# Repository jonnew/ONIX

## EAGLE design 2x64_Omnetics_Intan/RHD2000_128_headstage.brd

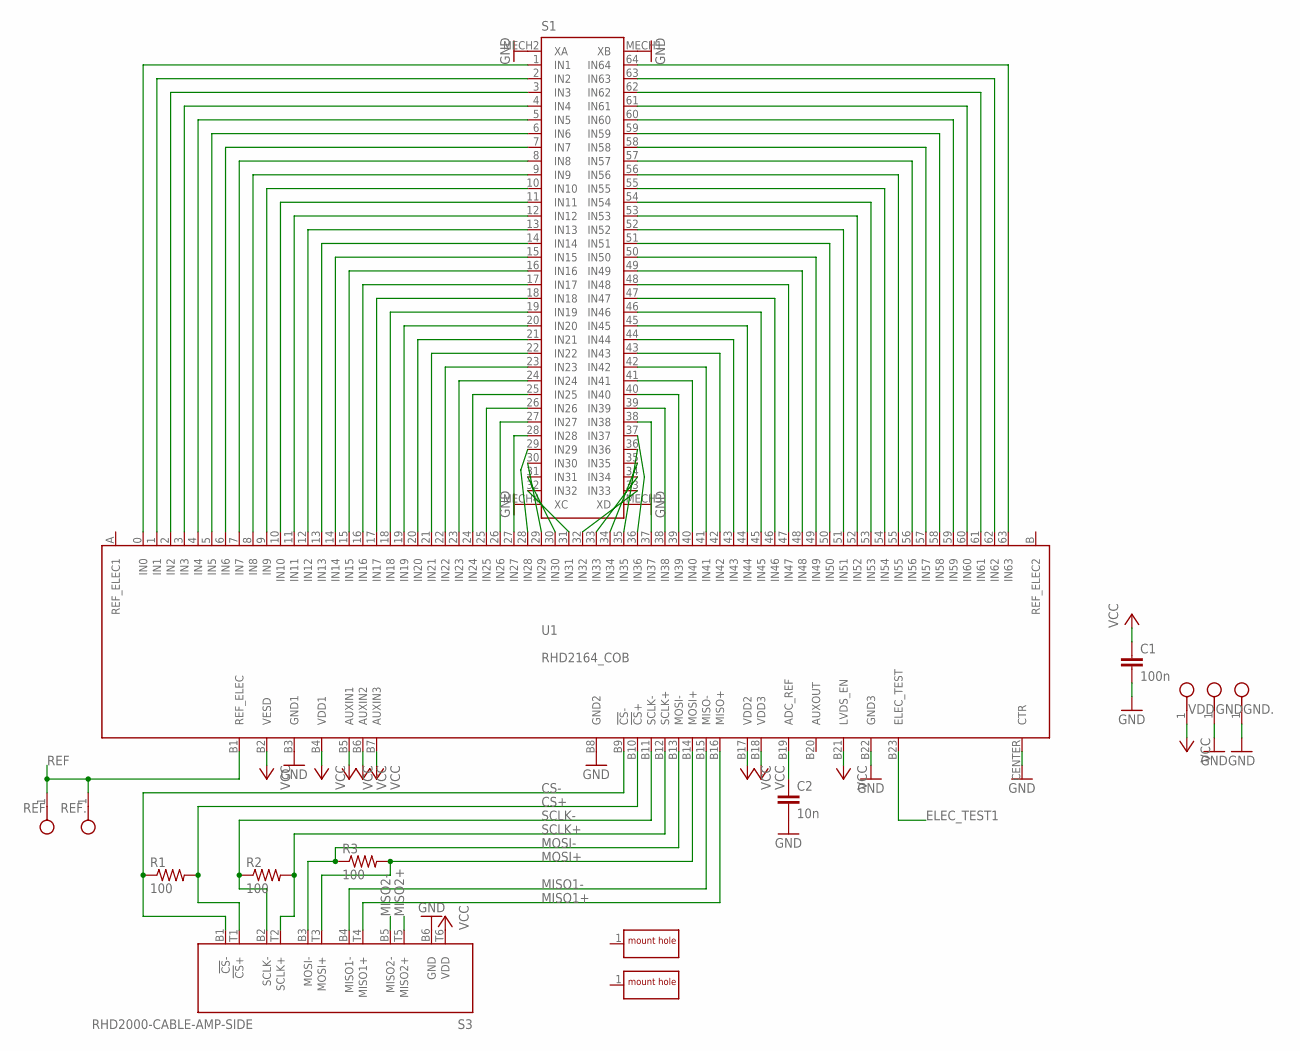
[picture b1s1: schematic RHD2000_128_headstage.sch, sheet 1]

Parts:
C1: 100n; 0402
C2: 10n; 0201
GND, GND.: TESTPOINT_SMALL
H1, H2: MOUNTING_HOLE_60MIL
R1, R2, R3: 100; 0201
REF, REF.: TESTPOINT_SMALL
S1: MOLEX_SLIMSTACK_64
S3: RHD2000-CABLE-AMP-SIDE; OMNETICS_PZN-12-AA
U1: RHD2164_COB
VDD: TESTPOINT_SMALL

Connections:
CS+: R1.2, S3.T1 (!CS!+), U1.B10 (!CS!+); also elsewhere on the board
CS-: R1.1, S3.B1 (!CS!-), U1.B9 (!CS!-); also elsewhere on the board
ELEC_TEST1: U1.B23 (ELEC_TEST); also elsewhere on the board
GND: C1.2, C2.2, GND.1, GND..1, S1.MECH1 (XB), S1.MECH2 (XA), S1.MECH3 (XD), S1.MECH4 (XC), S3.B6 (GND), U1.B3 (GND1), U1.B8 (GND2), U1.B22 (GND3), U1.CENTER (CTR); also elsewhere on the board
MISO1+: S3.T4 (MISO1+), U1.B16 (MISO+)
MISO1-: S3.B4 (MISO1-), U1.B15 (MISO-)
MISO2+: S3.T5 (MISO2+); also elsewhere on the board
MISO2-: S3.B5 (MISO2-); also elsewhere on the board
MOSI+: R3.2, S3.T3 (MOSI+), U1.B14 (MOSI+); also elsewhere on the board
MOSI-: R3.1, S3.B3 (MOSI-), U1.B13 (MOSI-); also elsewhere on the board
unnamed: S1.1 (IN1), U1.0 (IN0)
unnamed: S1.2 (IN2), U1.1 (IN1)
unnamed: S1.3 (IN3), U1.2 (IN2)
unnamed: S1.4 (IN4), U1.3 (IN3)
unnamed: S1.5 (IN5), U1.4 (IN4)
unnamed: S1.6 (IN6), U1.5 (IN5)
unnamed: S1.7 (IN7), U1.6 (IN6)
unnamed: S1.8 (IN8), U1.7 (IN7)
unnamed: S1.9 (IN9), U1.8 (IN8)
unnamed: S1.10 (IN10), U1.9 (IN9)
unnamed: S1.11 (IN11), U1.10 (IN10)
unnamed: S1.12 (IN12), U1.11 (IN11)
unnamed: S1.13 (IN13), U1.12 (IN12)
unnamed: S1.14 (IN14), U1.13 (IN13)
unnamed: S1.15 (IN15), U1.14 (IN14)
unnamed: S1.16 (IN16), U1.15 (IN15)
unnamed: S1.17 (IN17), U1.16 (IN16)
unnamed: S1.18 (IN18), U1.17 (IN17)
unnamed: S1.19 (IN19), U1.18 (IN18)
unnamed: S1.20 (IN20), U1.19 (IN19)
unnamed: S1.21 (IN21), U1.20 (IN20)
unnamed: S1.22 (IN22), U1.21 (IN21)
unnamed: S1.23 (IN23), U1.22 (IN22)
unnamed: S1.24 (IN24), U1.23 (IN23)
unnamed: S1.25 (IN25), U1.24 (IN24)
unnamed: S1.26 (IN26), U1.25 (IN25)
unnamed: S1.27 (IN27), U1.26 (IN26)
unnamed: S1.28 (IN28), U1.27 (IN27)
unnamed: S1.38 (IN38), U1.37 (IN37)
unnamed: S1.39 (IN39), U1.38 (IN38)
unnamed: S1.64 (IN64), U1.63 (IN63)
unnamed: S1.63 (IN63), U1.62 (IN62)
unnamed: S1.62 (IN62), U1.61 (IN61)
unnamed: C2.1, U1.B19 (ADC_REF)
unnamed: S1.61 (IN61), U1.60 (IN60)
unnamed: S1.60 (IN60), U1.59 (IN59)
unnamed: S1.59 (IN59), U1.58 (IN58)
unnamed: S1.58 (IN58), U1.57 (IN57)
unnamed: S1.57 (IN57), U1.56 (IN56)
unnamed: S1.56 (IN56), U1.55 (IN55)
unnamed: S1.55 (IN55), U1.54 (IN54)
unnamed: S1.54 (IN54), U1.53 (IN53)
unnamed: S1.53 (IN53), U1.52 (IN52)
unnamed: S1.52 (IN52), U1.51 (IN51)
unnamed: S1.51 (IN51), U1.50 (IN50)
unnamed: S1.50 (IN50), U1.49 (IN49)
unnamed: S1.49 (IN49), U1.48 (IN48)
unnamed: S1.48 (IN48), U1.47 (IN47)
unnamed: S1.47 (IN47), U1.46 (IN46)
unnamed: S1.46 (IN46), U1.45 (IN45)
unnamed: S1.45 (IN45), U1.44 (IN44)
unnamed: S1.44 (IN44), U1.43 (IN43)
unnamed: S1.43 (IN43), U1.42 (IN42)
unnamed: S1.42 (IN42), U1.41 (IN41)
unnamed: S1.41 (IN41), U1.40 (IN40)
unnamed: S1.40 (IN40), U1.39 (IN39)
unnamed: S1.32 (IN32), U1.31 (IN31)
unnamed: S1.31 (IN31), U1.30 (IN30)
unnamed: S1.30 (IN30), U1.29 (IN29)
unnamed: S1.29 (IN29), U1.28 (IN28)
unnamed: S1.33 (IN33), U1.32 (IN32)
unnamed: S1.34 (IN34), U1.33 (IN33)
unnamed: S1.35 (IN35), U1.34 (IN34)
unnamed: S1.36 (IN36), U1.35 (IN35)
unnamed: S1.37 (IN37), U1.36 (IN36)
REF: REF.1, REF..1, U1.B1 (REF_ELEC); also elsewhere on the board
SCLK+: R2.2, S3.T2 (SCLK+), U1.B12 (SCLK+); also elsewhere on the board
SCLK-: R2.1, S3.B2 (SCLK-), U1.B11 (SCLK-); also elsewhere on the board
VCC: C1.1, S3.T6 (VDD), U1.B2 (VESD), U1.B4 (VDD1), U1.B5 (AUXIN1), U1.B6 (AUXIN2), U1.B7 (AUXIN3), U1.B17 (VDD2), U1.B18 (VDD3), U1.B21 (LVDS_EN), VDD.1; also elsewhere on the board

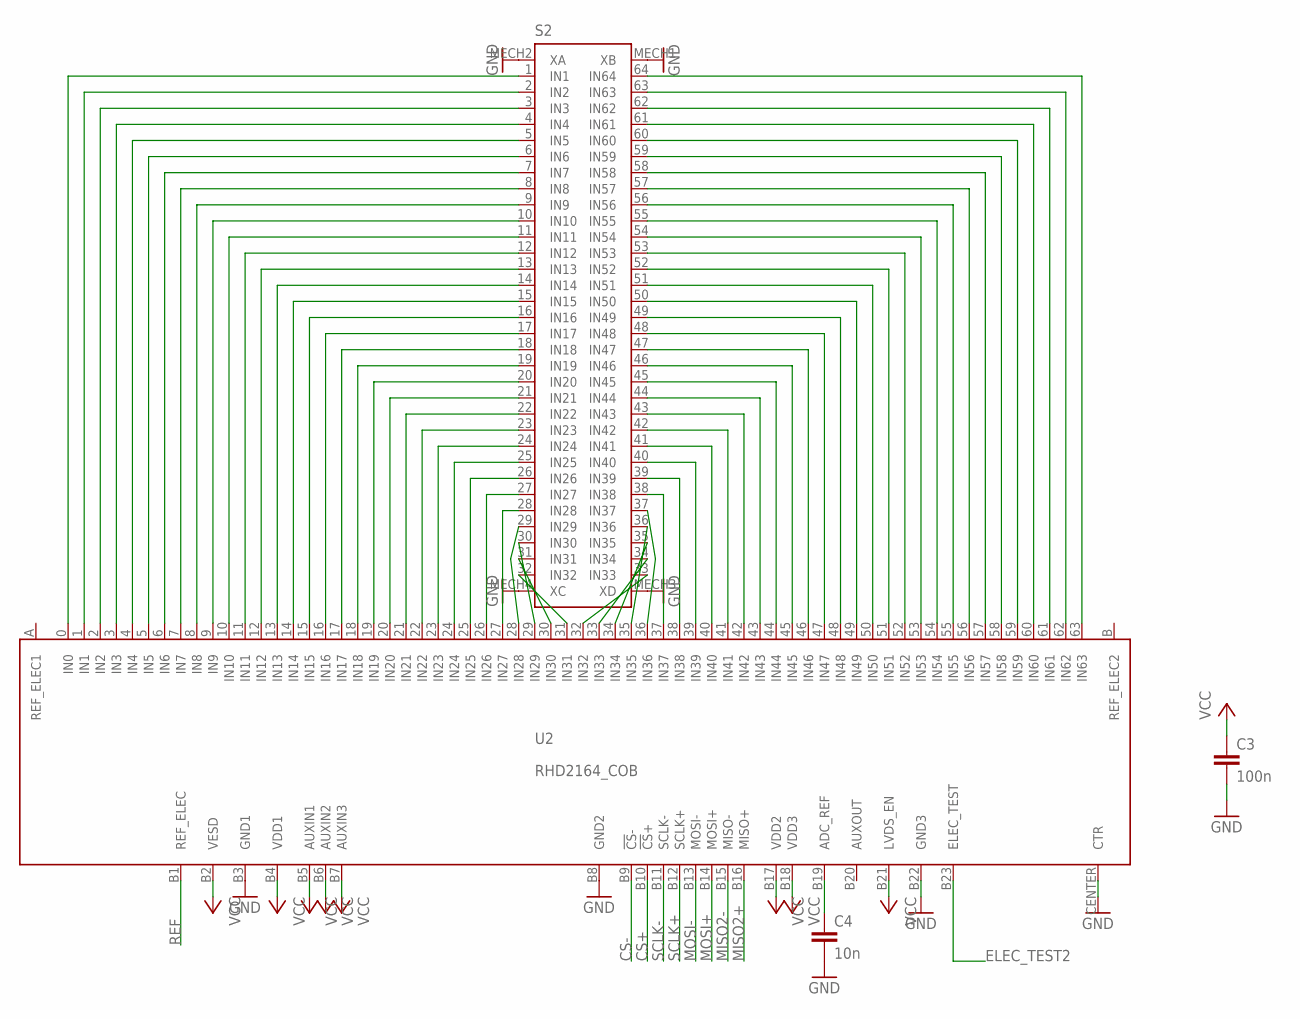
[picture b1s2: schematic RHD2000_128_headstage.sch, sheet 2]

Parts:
C3: 100n; 0402
C4: 10n; 0201
S2: MOLEX_SLIMSTACK_64
U2: RHD2164_COB

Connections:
CS+: U2.B10 (!CS!+); also elsewhere on the board
CS-: U2.B9 (!CS!-); also elsewhere on the board
ELEC_TEST2: U2.B23 (ELEC_TEST); also elsewhere on the board
GND: C3.2, C4.2, S2.MECH1 (XB), S2.MECH2 (XA), S2.MECH3 (XD), S2.MECH4 (XC), U2.B3 (GND1), U2.B8 (GND2), U2.B22 (GND3), U2.CENTER (CTR); also elsewhere on the board
MISO2+: U2.B16 (MISO+); also elsewhere on the board
MISO2-: U2.B15 (MISO-); also elsewhere on the board
MOSI+: U2.B14 (MOSI+); also elsewhere on the board
MOSI-: U2.B13 (MOSI-); also elsewhere on the board
unnamed: C4.1, U2.B19 (ADC_REF)
unnamed: S2.1 (IN1), U2.0 (IN0)
unnamed: S2.2 (IN2), U2.1 (IN1)
unnamed: S2.3 (IN3), U2.2 (IN2)
unnamed: S2.4 (IN4), U2.3 (IN3)
unnamed: S2.5 (IN5), U2.4 (IN4)
unnamed: S2.6 (IN6), U2.5 (IN5)
unnamed: S2.7 (IN7), U2.6 (IN6)
unnamed: S2.8 (IN8), U2.7 (IN7)
unnamed: S2.9 (IN9), U2.8 (IN8)
unnamed: S2.10 (IN10), U2.9 (IN9)
unnamed: S2.11 (IN11), U2.10 (IN10)
unnamed: S2.12 (IN12), U2.11 (IN11)
unnamed: S2.13 (IN13), U2.12 (IN12)
unnamed: S2.14 (IN14), U2.13 (IN13)
unnamed: S2.15 (IN15), U2.14 (IN14)
unnamed: S2.16 (IN16), U2.15 (IN15)
unnamed: S2.17 (IN17), U2.16 (IN16)
unnamed: S2.18 (IN18), U2.17 (IN17)
unnamed: S2.19 (IN19), U2.18 (IN18)
unnamed: S2.20 (IN20), U2.19 (IN19)
unnamed: S2.21 (IN21), U2.20 (IN20)
unnamed: S2.22 (IN22), U2.21 (IN21)
unnamed: S2.23 (IN23), U2.22 (IN22)
unnamed: S2.24 (IN24), U2.23 (IN23)
unnamed: S2.25 (IN25), U2.24 (IN24)
unnamed: S2.26 (IN26), U2.25 (IN25)
unnamed: S2.27 (IN27), U2.26 (IN26)
unnamed: S2.28 (IN28), U2.27 (IN27)
unnamed: S2.38 (IN38), U2.37 (IN37)
unnamed: S2.39 (IN39), U2.38 (IN38)
unnamed: S2.64 (IN64), U2.63 (IN63)
unnamed: S2.63 (IN63), U2.62 (IN62)
unnamed: S2.62 (IN62), U2.61 (IN61)
unnamed: S2.61 (IN61), U2.60 (IN60)
unnamed: S2.60 (IN60), U2.59 (IN59)
unnamed: S2.59 (IN59), U2.58 (IN58)
unnamed: S2.58 (IN58), U2.57 (IN57)
unnamed: S2.57 (IN57), U2.56 (IN56)
unnamed: S2.56 (IN56), U2.55 (IN55)
unnamed: S2.55 (IN55), U2.54 (IN54)
unnamed: S2.54 (IN54), U2.53 (IN53)
unnamed: S2.53 (IN53), U2.52 (IN52)
unnamed: S2.52 (IN52), U2.51 (IN51)
unnamed: S2.51 (IN51), U2.50 (IN50)
unnamed: S2.50 (IN50), U2.49 (IN49)
unnamed: S2.49 (IN49), U2.48 (IN48)
unnamed: S2.48 (IN48), U2.47 (IN47)
unnamed: S2.47 (IN47), U2.46 (IN46)
unnamed: S2.46 (IN46), U2.45 (IN45)
unnamed: S2.45 (IN45), U2.44 (IN44)
unnamed: S2.44 (IN44), U2.43 (IN43)
unnamed: S2.43 (IN43), U2.42 (IN42)
unnamed: S2.42 (IN42), U2.41 (IN41)
unnamed: S2.41 (IN41), U2.40 (IN40)
unnamed: S2.40 (IN40), U2.39 (IN39)
unnamed: S2.32 (IN32), U2.31 (IN31)
unnamed: S2.31 (IN31), U2.30 (IN30)
unnamed: S2.30 (IN30), U2.29 (IN29)
unnamed: S2.29 (IN29), U2.28 (IN28)
unnamed: S2.33 (IN33), U2.32 (IN32)
unnamed: S2.34 (IN34), U2.33 (IN33)
unnamed: S2.35 (IN35), U2.34 (IN34)
unnamed: S2.36 (IN36), U2.35 (IN35)
unnamed: S2.37 (IN37), U2.36 (IN36)
REF: U2.B1 (REF_ELEC); also elsewhere on the board
SCLK+: U2.B12 (SCLK+); also elsewhere on the board
SCLK-: U2.B11 (SCLK-); also elsewhere on the board
VCC: C3.1, U2.B2 (VESD), U2.B4 (VDD1), U2.B5 (AUXIN1), U2.B6 (AUXIN2), U2.B7 (AUXIN3), U2.B17 (VDD2), U2.B18 (VDD3), U2.B21 (LVDS_EN); also elsewhere on the board

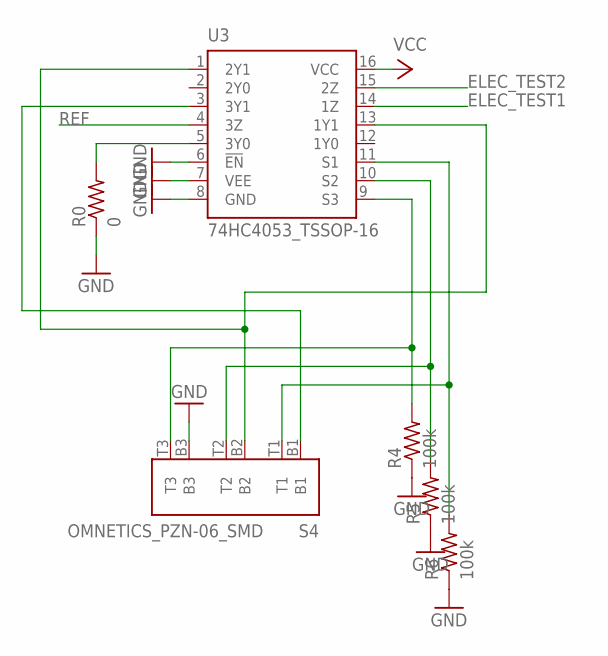
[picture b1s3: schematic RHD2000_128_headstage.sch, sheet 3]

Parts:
R0: 0; 0402
R4, R5, R6: 100k; 0201
S4: OMNETICS_PZN-06_SMD; OMNETICS_PZN-06-AA
U3: 74HC4053_TSSOP-16; TSSOP-16

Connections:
ELEC_TEST1: U3.14 (1Z); also elsewhere on the board
ELEC_TEST2: U3.15 (2Z); also elsewhere on the board
GND: R0.1, R4.1, R5.1, R6.1, S4.B3, U3.6 (!EN!), U3.7 (VEE), U3.8 (GND); also elsewhere on the board
unnamed: R6.2, S4.T1, U3.11 (S1)
unnamed: R5.2, S4.T2, U3.10 (S2)
unnamed: R4.2, S4.T3, U3.9 (S3)
unnamed: R0.2, U3.5 (3Y0)
unnamed: S4.B1, U3.3 (3Y1)
unnamed: S4.B2, U3.1 (2Y1), U3.13 (1Y1)
REF: U3.4 (3Z); also elsewhere on the board
VCC: U3.16 (VCC); also elsewhere on the board

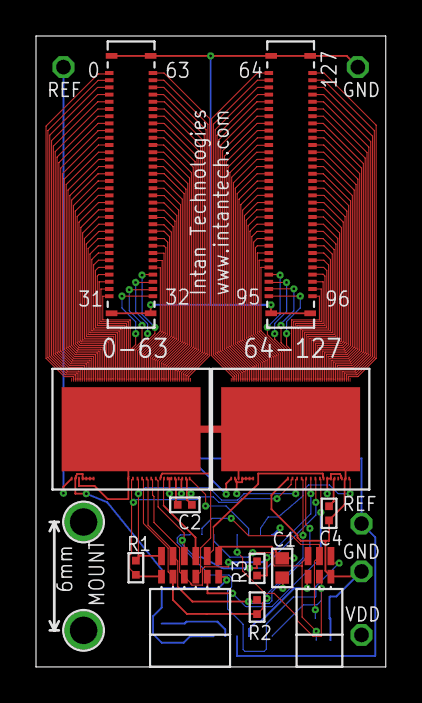
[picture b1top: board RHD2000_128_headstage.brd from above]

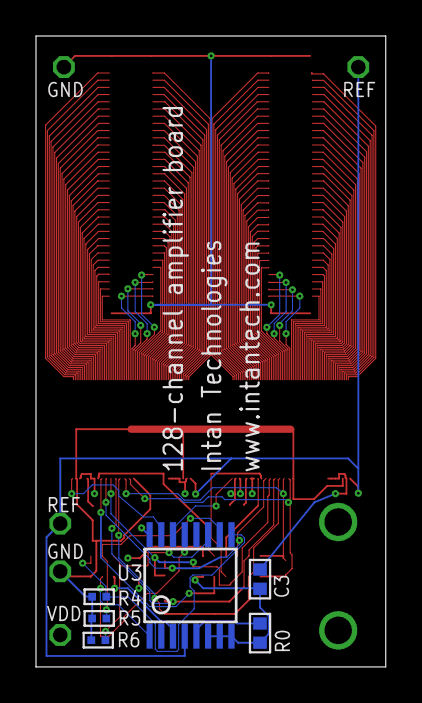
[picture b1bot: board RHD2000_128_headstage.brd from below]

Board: 4 copper layers, 19.4 x 35.1 mm, 25 parts (6 on the bottom side), 151 nets.

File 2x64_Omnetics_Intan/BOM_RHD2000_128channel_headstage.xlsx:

Bill of Materials |  | RHD2000 128-Channel Headstage Board |  | Intan Technologies
Part | Value | Device | Package | Digi-Key part number | Notes
C1 | 100 nF (0.1 uF) | ceramic capacitor (25 V) | 0402 | 445-4964-1-ND
C2 | 10 nF (10000 pF) | ceramic capacitor (16 V) | 0201 | 311-1404-1-ND
C3 | 100 nF (0.1 uF) | ceramic capacitor (25 V) | 0402 | 445-4964-1-ND
C4 | 10 nF (10000 pF) | ceramic capacitor (16 V) | 0201 | 311-1404-1-ND
R0 | 0 | resistor | 0402 | P0.0JCT-ND
R1 | 100 | resistor | 0201 | P100AGCT-ND
R2 | 100 | resistor | 0201 | P100AGCT-ND
R3 | 100 | resistor | 0201 | P100AGCT-ND
R4 | 75k | resistor | 0201 | P75KAGCT-ND
R5 | 75k | resistor | 0201 | P75KAGCT-ND
R6 | 75k | resistor | 0201 | P75KAGCT-ND
S1 | 64-pin vertical connector | Molex SlimStack connector | 64-pin vertical | WM24076-ND | mating connector: WM24084-ND
S2 | 64-pin vertical connector | Molex SlimStack connector | 64-pin vertical | WM24076-ND | mating connector: WM24084-ND
S3 | PZN-12-AA | polarized nano connector | polarized 12-pin | Omnetics A79623-001
S4 | PZN-06-AA | polarized nano connector | polarized 6-pin | Omnetics A79008-001
U1 | RHD2164 | 64-channel amplifier chip | QFN-56L | Intan RHD2164
U1 | RHD2164 | 64-channel amplifier chip | QFN-56L | Intan RHD2164
U3 | 74HC4053 | triple 2:1 MUX/DEMUX | TSSOP-16 | 568-4478-1-ND

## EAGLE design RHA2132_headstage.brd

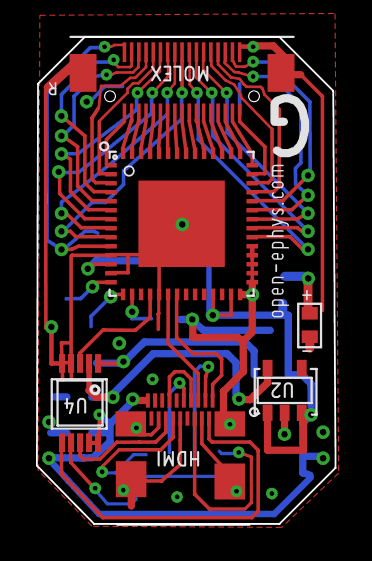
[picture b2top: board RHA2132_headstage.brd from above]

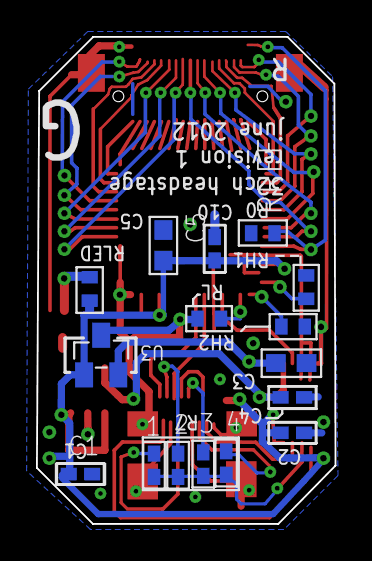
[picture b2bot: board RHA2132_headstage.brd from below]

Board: 2 copper layers, 16.6 x 27.1 mm, 22 parts (16 on the bottom side), 9 nets.

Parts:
1, 2, 3, 4: C0402
C1: C0402
C5: C0603
C_ADC_1: C0402
C_REG, C_REG1: C0402
C_VREF: C0603
E$1: MICRO_HDMI
E$2: MOLEX_5033763410
LED: R0402
LED_R: R0402
RH1: RH1; R0402
RH2: RH2; R0402
RL: RL; R0402
RREF: R0402
U2: ADP1710; TSOT-23-5
U3: ADR381; SOT23
U4: AD7980-MSOP; MSOP-10
U5: RHA2132QFN; QFN56_8_X_8

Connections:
AGND: C1.2, C5.2, C_VREF.2, RH1.1, RH2.1, RREF.2, U2.2, U4.4, U4.5, U5.11, U5.13, U5.28, U5.29, U5.30, U5.31, U5.32, U5.33, U5.CENTER
MUX_OUT: U4.3, U5.18
S$5: U4.9, U4.10
SETH1: RH1.2, U5.14
SETH2: RH2.2, U5.15
SETL: RL.2, U5.16
VDD: C1.1, C5.1, U2.1, U2.3, U3.1, U5.12, U5.25, U5.27
VREG_V: C_REG.1, U2.5, U4.2
V_REF: C_VREF.1, U3.2, U4.1

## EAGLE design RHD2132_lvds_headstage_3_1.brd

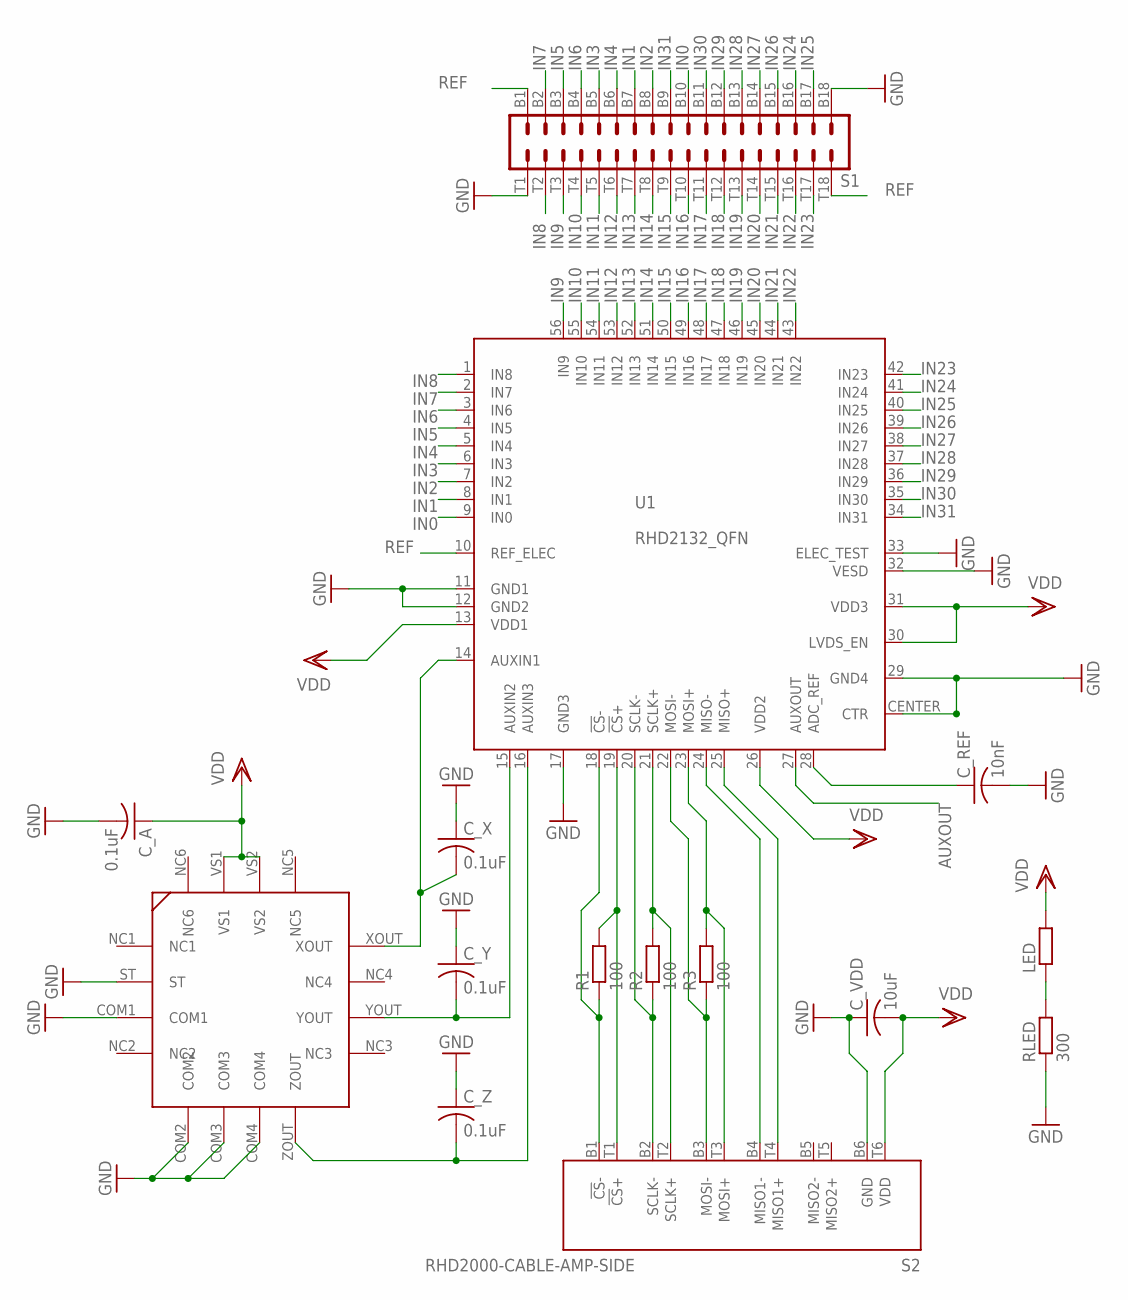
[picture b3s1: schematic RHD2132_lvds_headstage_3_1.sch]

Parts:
C_A: 0.1uF; C0402K
C_REF: 10nF; C0402K
C_VDD: 10uF; C0402K
C_X: 0.1uF; C0402K
C_Y: 0.1uF; C0402K
C_Z: 0.1uF; C0402K
LED: R-EU_R0402; R0402
R1, R2, R3: 100; R0402
RLED: 300; R0402
S1: OMNETICS_A79025
S2: RHD2000-CABLE-AMP-SIDE; OMNETICS_PZN-12-AA
U1: RHD2132_QFN; QFN56_8_X_8_LARGE
U$1: ADXL335

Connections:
ADC_REF: C_REF.1, U1.28 (ADC_REF)
AUXOUT: U1.27 (AUXOUT)
CS+: R1.2, S2.T1 (!CS!+), U1.19 (!CS!+)
CS-: R1.1, S2.B1 (!CS!-), U1.18 (!CS!-)
IN0: S1.B10, U1.9 (IN0)
IN1: S1.B7, U1.8 (IN1)
IN2: S1.B8, U1.7 (IN2)
IN3: S1.B5, U1.6 (IN3)
IN4: S1.B6, U1.5 (IN4)
IN5: S1.B3, U1.4 (IN5)
IN6: S1.B4, U1.3 (IN6)
IN7: S1.B2, U1.2 (IN7)
IN8: S1.T2, U1.1 (IN8)
IN9: S1.T3, U1.56 (IN9)
IN10: S1.T4, U1.55 (IN10)
IN11: S1.T5, U1.54 (IN11)
IN12: S1.T6, U1.53 (IN12)
IN13: S1.T7, U1.52 (IN13)
IN14: S1.T8, U1.51 (IN14)
IN15: S1.T9, U1.50 (IN15)
IN16: S1.T10, U1.49 (IN16)
IN17: S1.T11, U1.48 (IN17)
IN18: S1.T12, U1.47 (IN18)
IN19: S1.T13, U1.46 (IN19)
IN20: S1.T14, U1.45 (IN20)
IN21: S1.T15, U1.44 (IN21)
IN22: S1.T16, U1.43 (IN22)
IN23: S1.T17, U1.42 (IN23)
IN24: S1.B16, U1.41 (IN24)
IN25: S1.B17, U1.40 (IN25)
IN26: S1.B15, U1.39 (IN26)
IN27: S1.B14, U1.38 (IN27)
IN28: S1.B13, U1.37 (IN28)
IN29: S1.B12, U1.36 (IN29)
IN30: S1.B11, U1.35 (IN30)
IN31: S1.B9, U1.34 (IN31)
LEDOUT: LED.1, RLED.2
MISO1+: S2.T4 (MISO1+), U1.25 (MISO+)
MISO1-: S2.B4 (MISO1-), U1.24 (MISO-)
MOSI+: R3.2, S2.T3 (MOSI+), U1.23 (MOSI+)
MOSI-: R3.1, S2.B3 (MOSI-), U1.22 (MOSI-)
SCLK+: R2.2, S2.T2 (SCLK+), U1.21 (SCLK+)
SCLK-: R2.1, S2.B2 (SCLK-), U1.20 (SCLK-)
VDD: C_A.1, C_VDD.2, LED.2, S2.T6 (VDD), U1.13 (VDD1), U1.26 (VDD2), U1.30 (LVDS_EN), U1.31 (VDD3), U$1.VS1, U$1.VS2
XOUT: C_X.2, U1.14 (AUXIN1), U$1.XOUT
YOUT: C_Y.2, U1.15 (AUXIN2), U$1.YOUT
ZOUT: C_Z.2, U1.16 (AUXIN3), U$1.ZOUT

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
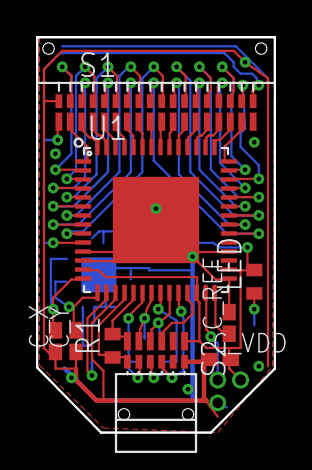
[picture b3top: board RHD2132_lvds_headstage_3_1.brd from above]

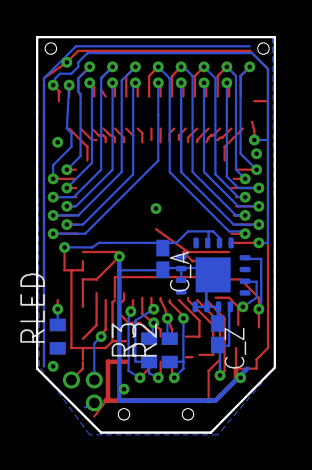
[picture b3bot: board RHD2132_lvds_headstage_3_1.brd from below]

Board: 2 copper layers, 13.2 x 22.0 mm, 15 parts (6 on the bottom side), 48 nets.

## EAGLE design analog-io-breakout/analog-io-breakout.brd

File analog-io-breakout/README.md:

# Analog IO Breakout Board
This board allows easy bench-top access to the analog IO provided by the
[fmc-host board](../fmc-host/README.md). It features

- BNC, SMA, ribbon, or direct wire access to 16 analog inputs and 8 analog
  outputs
- Rugged M6 or 1/4-20 mounting options compliant with 19" racks and optical
  tables
- 3D printed case

## Gerber Files
{% include gerber_layers.md %}

## Bill of Materials
The bill of materials for this device can be found
[here](https://docs.google.com/spreadsheets/d/18WfmbLGt8bGUUdksKp6AKA_wMX2SJ3Tndin-nnEgUCs/edit?usp=sharing).

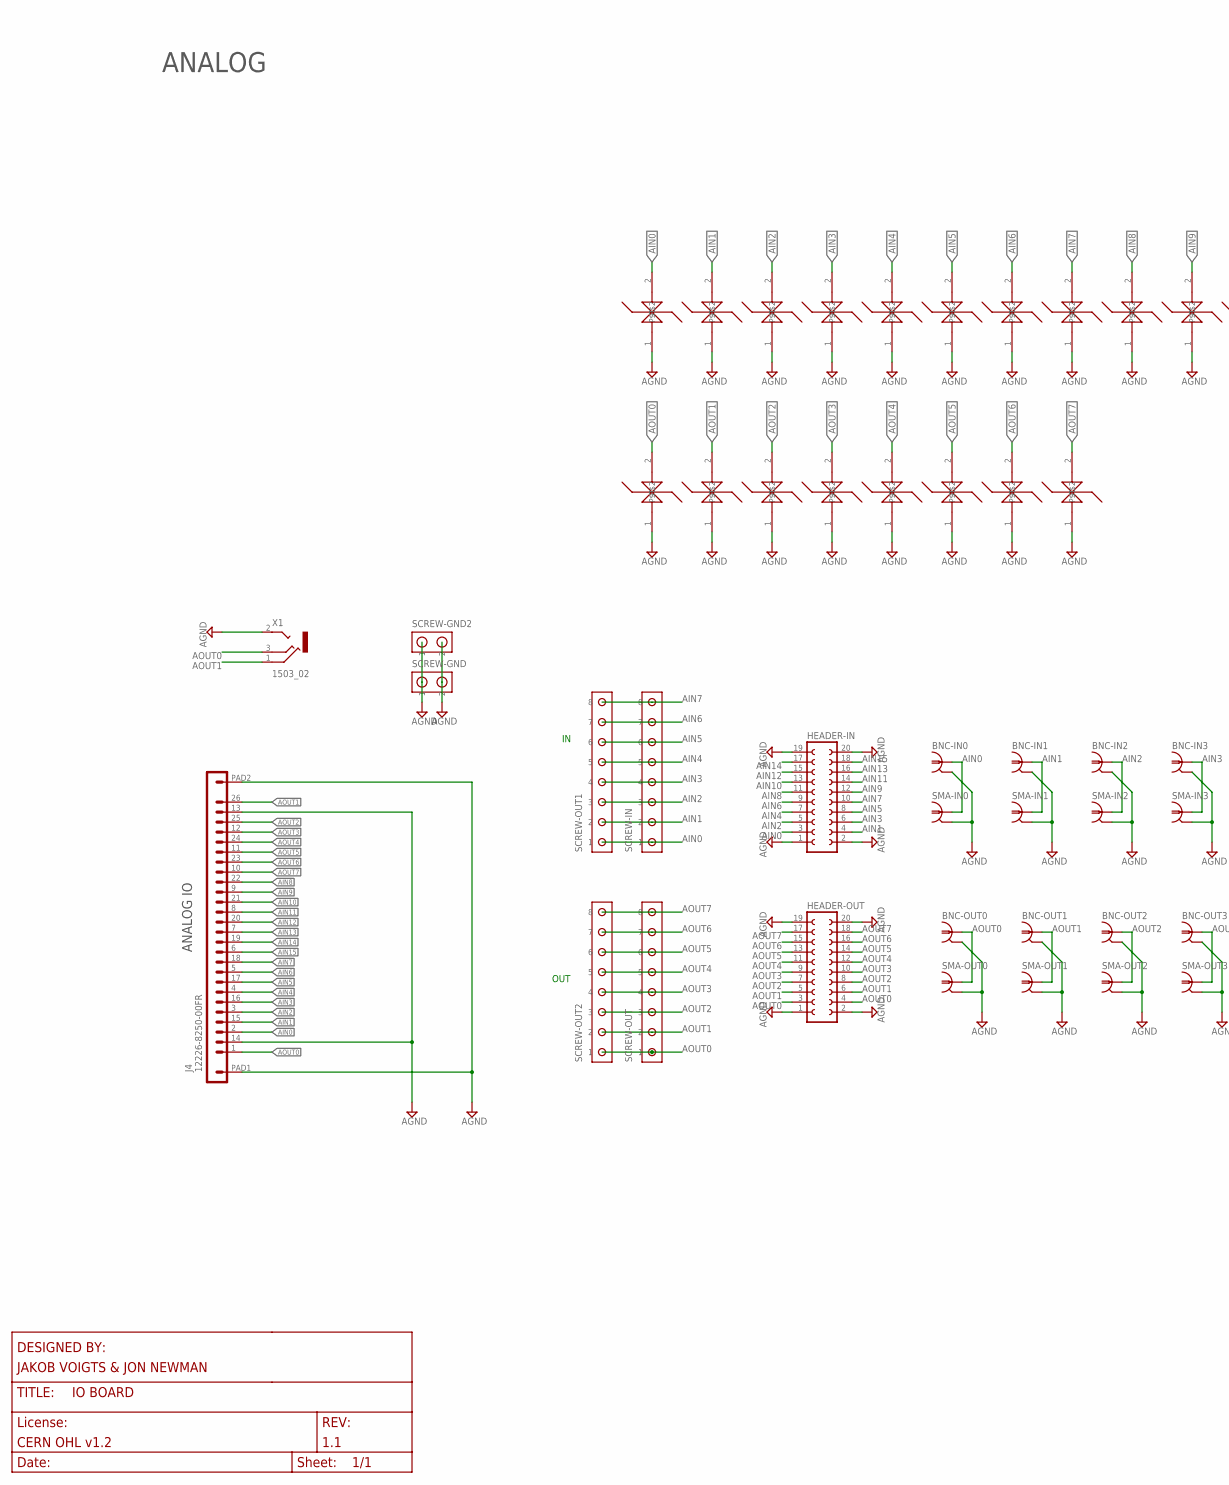
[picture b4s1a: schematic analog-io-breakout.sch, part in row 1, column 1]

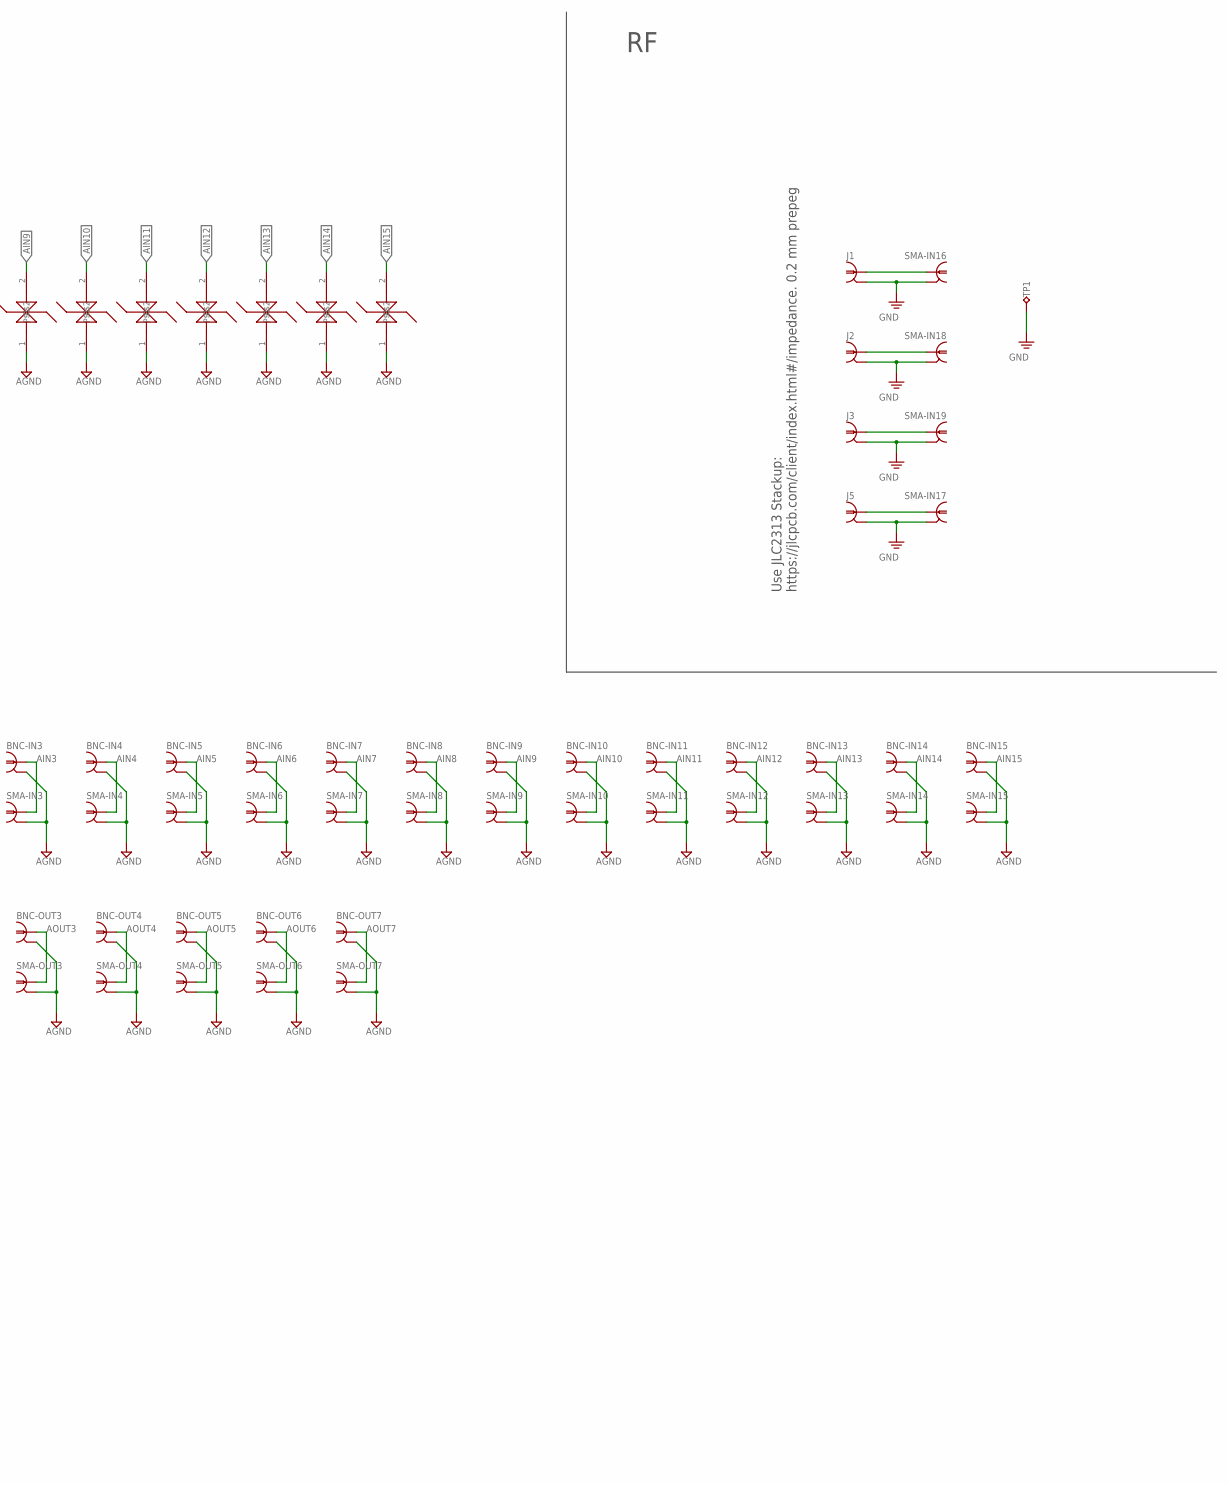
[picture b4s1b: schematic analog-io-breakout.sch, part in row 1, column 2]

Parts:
BNC-IN0, BNC-IN1, BNC-IN2, BNC-IN3, BNC-IN4, BNC-IN5, BNC-IN6, BNC-IN7, BNC-IN8, BNC-IN9, BNC-IN10, BNC-IN11, BNC-IN12, BNC-IN13, BNC-IN14, BNC-IN15: COAX_B35N61-LARGE-HOLES; B35N61_LARGE-HOLES
BNC-OUT0, BNC-OUT1, BNC-OUT2, BNC-OUT3, BNC-OUT4, BNC-OUT5, BNC-OUT6, BNC-OUT7: COAX_B35N61-LARGE-HOLES; B35N61_LARGE-HOLES
HEADER-IN: FE10-2
HEADER-OUT: FE10-2
J1, J2, J3, J5: COAX_MMCX-RA; MMCX-J-P-X-RA-SM1
J4: 12226-8250-00FR; 12226-82X0-00XX
SCREW-GND, SCREW-GND2: SCREW2
SCREW-IN: SCREW8
SCREW-OUT, SCREW-OUT1, SCREW-OUT2: SCREW8
SMA-IN0, SMA-IN1, SMA-IN2, SMA-IN3, SMA-IN4, SMA-IN5, SMA-IN6, SMA-IN7, SMA-IN8, SMA-IN9, SMA-IN10, SMA-IN11, SMA-IN12, SMA-IN13, SMA-IN14, SMA-IN15, SMA-IN16, SMA-IN17, SMA-IN18, SMA-IN19: COAX_SMA-VERT; SMA_JACK_142-0701-201
SMA-OUT0, SMA-OUT1, SMA-OUT2, SMA-OUT3, SMA-OUT4, SMA-OUT5, SMA-OUT6, SMA-OUT7: COAX_SMA-VERT; SMA_JACK_142-0701-201
TP1: TP_2MM; TESTPOINT_2MM
U$1, U$2, U$3, U$4, U$5, U$6, U$7, U$8, U$9, U$10, U$11, U$12, U$13, U$14, U$15, U$16, U$17, U$18, U$19, U$20, U$21, U$22, U$23, U$24: DIODE-ESD-BIDIRECTIONALDO-214AA; DIOC7026X260
X1: 1503_02

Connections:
AGND: BNC-IN0.2, BNC-IN0.3 (2), BNC-IN0.4 (2), BNC-IN0.5 (2), BNC-IN1.2, BNC-IN1.3 (2), BNC-IN1.4 (2), BNC-IN1.5 (2), BNC-IN2.2, BNC-IN2.3 (2), BNC-IN2.4 (2), BNC-IN2.5 (2), BNC-IN3.2, BNC-IN3.3 (2), BNC-IN3.4 (2), BNC-IN3.5 (2), BNC-IN4.2, BNC-IN4.3 (2), BNC-IN4.4 (2), BNC-IN4.5 (2), BNC-IN5.2, BNC-IN5.3 (2), BNC-IN5.4 (2), BNC-IN5.5 (2), BNC-IN6.2, BNC-IN6.3 (2), BNC-IN6.4 (2), BNC-IN6.5 (2), BNC-IN7.2, BNC-IN7.3 (2), BNC-IN7.4 (2), BNC-IN7.5 (2), BNC-IN8.2, BNC-IN8.3 (2), BNC-IN8.4 (2), BNC-IN8.5 (2), BNC-IN9.2, BNC-IN9.3 (2), BNC-IN9.4 (2), BNC-IN9.5 (2), BNC-IN10.2, BNC-IN10.3 (2), BNC-IN10.4 (2), BNC-IN10.5 (2), BNC-IN11.2, BNC-IN11.3 (2), BNC-IN11.4 (2), BNC-IN11.5 (2), BNC-IN12.2, BNC-IN12.3 (2), BNC-IN12.4 (2), BNC-IN12.5 (2), BNC-IN13.2, BNC-IN13.3 (2), BNC-IN13.4 (2), BNC-IN13.5 (2), BNC-IN14.2, BNC-IN14.3 (2), BNC-IN14.4 (2), BNC-IN14.5 (2), BNC-IN15.2, BNC-IN15.3 (2), BNC-IN15.4 (2), BNC-IN15.5 (2), BNC-OUT0.2, BNC-OUT0.3 (2), BNC-OUT0.4 (2), BNC-OUT0.5 (2), BNC-OUT1.2, BNC-OUT1.3 (2), BNC-OUT1.4 (2), BNC-OUT1.5 (2), BNC-OUT2.2, BNC-OUT2.3 (2), BNC-OUT2.4 (2), BNC-OUT2.5 (2), BNC-OUT3.2, BNC-OUT3.3 (2), BNC-OUT3.4 (2), BNC-OUT3.5 (2), BNC-OUT4.2, BNC-OUT4.3 (2), BNC-OUT4.4 (2), BNC-OUT4.5 (2), BNC-OUT5.2, BNC-OUT5.3 (2), BNC-OUT5.4 (2), BNC-OUT5.5 (2), BNC-OUT6.2, BNC-OUT6.3 (2), BNC-OUT6.4 (2), BNC-OUT6.5 (2), BNC-OUT7.2, BNC-OUT7.3 (2), BNC-OUT7.4 (2), BNC-OUT7.5 (2), HEADER-IN.1, HEADER-IN.2, HEADER-IN.19, HEADER-IN.20, HEADER-OUT.1, HEADER-OUT.2, HEADER-OUT.19, HEADER-OUT.20, J4.13, J4.14, J4.PAD1, J4.PAD2, SCREW-GND.P$1 (1), SCREW-GND.P$2 (2), SCREW-GND2.P$1 (1), SCREW-GND2.P$2 (2), SMA-IN0.GND$1 (2), SMA-IN0.GND$2 (2), SMA-IN0.GND$3 (2), SMA-IN0.GND$4 (2), SMA-IN1.GND$1 (2), SMA-IN1.GND$2 (2), SMA-IN1.GND$3 (2), SMA-IN1.GND$4 (2), SMA-IN2.GND$1 (2), SMA-IN2.GND$2 (2), SMA-IN2.GND$3 (2), SMA-IN2.GND$4 (2), SMA-IN3.GND$1 (2), SMA-IN3.GND$2 (2), SMA-IN3.GND$3 (2), SMA-IN3.GND$4 (2), SMA-IN4.GND$1 (2), SMA-IN4.GND$2 (2), SMA-IN4.GND$3 (2), SMA-IN4.GND$4 (2), SMA-IN5.GND$1 (2), SMA-IN5.GND$2 (2), SMA-IN5.GND$3 (2), SMA-IN5.GND$4 (2), SMA-IN6.GND$1 (2), SMA-IN6.GND$2 (2), SMA-IN6.GND$3 (2), SMA-IN6.GND$4 (2), SMA-IN7.GND$1 (2), SMA-IN7.GND$2 (2), SMA-IN7.GND$3 (2), SMA-IN7.GND$4 (2), SMA-IN8.GND$1 (2), SMA-IN8.GND$2 (2), SMA-IN8.GND$3 (2), SMA-IN8.GND$4 (2), SMA-IN9.GND$1 (2), SMA-IN9.GND$2 (2), SMA-IN9.GND$3 (2), SMA-IN9.GND$4 (2), SMA-IN10.GND$1 (2), SMA-IN10.GND$2 (2), SMA-IN10.GND$3 (2), SMA-IN10.GND$4 (2), SMA-IN11.GND$1 (2), SMA-IN11.GND$2 (2), SMA-IN11.GND$3 (2), SMA-IN11.GND$4 (2), SMA-IN12.GND$1 (2), SMA-IN12.GND$2 (2), SMA-IN12.GND$3 (2), SMA-IN12.GND$4 (2), SMA-IN13.GND$1 (2), SMA-IN13.GND$2 (2), SMA-IN13.GND$3 (2), SMA-IN13.GND$4 (2), SMA-IN14.GND$1 (2), SMA-IN14.GND$2 (2), SMA-IN14.GND$3 (2), SMA-IN14.GND$4 (2), SMA-IN15.GND$1 (2), SMA-IN15.GND$2 (2), SMA-IN15.GND$3 (2), SMA-IN15.GND$4 (2), SMA-OUT0.GND$1 (2), SMA-OUT0.GND$2 (2), SMA-OUT0.GND$3 (2), SMA-OUT0.GND$4 (2), SMA-OUT1.GND$1 (2), SMA-OUT1.GND$2 (2), SMA-OUT1.GND$3 (2), SMA-OUT1.GND$4 (2), SMA-OUT2.GND$1 (2), SMA-OUT2.GND$2 (2), SMA-OUT2.GND$3 (2), SMA-OUT2.GND$4 (2), SMA-OUT3.GND$1 (2), SMA-OUT3.GND$2 (2), SMA-OUT3.GND$3 (2), SMA-OUT3.GND$4 (2), SMA-OUT4.GND$1 (2), SMA-OUT4.GND$2 (2), SMA-OUT4.GND$3 (2), SMA-OUT4.GND$4 (2), SMA-OUT5.GND$1 (2), SMA-OUT5.GND$2 (2), SMA-OUT5.GND$3 (2), SMA-OUT5.GND$4 (2), SMA-OUT6.GND$1 (2), SMA-OUT6.GND$2 (2), SMA-OUT6.GND$3 (2), SMA-OUT6.GND$4 (2), SMA-OUT7.GND$1 (2), SMA-OUT7.GND$2 (2), SMA-OUT7.GND$3 (2), SMA-OUT7.GND$4 (2), U$1.1, U$2.1, U$3.1, U$4.1, U$5.1, U$6.1, U$7.1, U$8.1, U$9.1, U$10.1, U$11.1, U$12.1, U$13.1, U$14.1, U$15.1, U$16.1, U$17.1, U$18.1, U$19.1, U$20.1, U$21.1, U$22.1, U$23.1, U$24.1, X1.2
AIN0: BNC-IN0.1, HEADER-IN.3, J4.2, SCREW-IN.1, SCREW-OUT1.1, SMA-IN0.CLK (1), U$1.2
AIN1: BNC-IN1.1, HEADER-IN.4, J4.15, SCREW-IN.2, SCREW-OUT1.2, SMA-IN1.CLK (1), U$2.2
AIN2: BNC-IN2.1, HEADER-IN.5, J4.3, SCREW-IN.3, SCREW-OUT1.3, SMA-IN2.CLK (1), U$3.2
AIN3: BNC-IN3.1, HEADER-IN.6, J4.16, SCREW-IN.4, SCREW-OUT1.4, SMA-IN3.CLK (1), U$4.2
AIN4: BNC-IN4.1, HEADER-IN.7, J4.4, SCREW-IN.5, SCREW-OUT1.5, SMA-IN4.CLK (1), U$5.2
AIN5: BNC-IN5.1, HEADER-IN.8, J4.17, SCREW-IN.6, SCREW-OUT1.6, SMA-IN5.CLK (1), U$6.2
AIN6: BNC-IN6.1, HEADER-IN.9, J4.5, SCREW-IN.7, SCREW-OUT1.7, SMA-IN6.CLK (1), U$7.2
AIN7: BNC-IN7.1, HEADER-IN.10, J4.18, SCREW-IN.8, SCREW-OUT1.8, SMA-IN7.CLK (1), U$8.2
AIN8: BNC-IN8.1, HEADER-IN.11, J4.22, SMA-IN8.CLK (1), U$17.2
AIN9: BNC-IN9.1, HEADER-IN.12, J4.9, SMA-IN9.CLK (1), U$18.2
AIN10: BNC-IN10.1, HEADER-IN.13, J4.21, SMA-IN10.CLK (1), U$19.2
AIN11: BNC-IN11.1, HEADER-IN.14, J4.8, SMA-IN11.CLK (1), U$20.2
AIN12: BNC-IN12.1, HEADER-IN.15, J4.20, SMA-IN12.CLK (1), U$21.2
AIN13: BNC-IN13.1, HEADER-IN.16, J4.7, SMA-IN13.CLK (1), U$22.2
AIN14: BNC-IN14.1, HEADER-IN.17, J4.19, SMA-IN14.CLK (1), U$23.2
AIN15: BNC-IN15.1, HEADER-IN.18, J4.6, SMA-IN15.CLK (1), U$24.2
AOUT0: BNC-OUT0.1, HEADER-OUT.3, HEADER-OUT.4, J4.1, SCREW-OUT.1, SCREW-OUT2.1, SMA-OUT0.CLK (1), U$9.2, X1.3
AOUT1: BNC-OUT1.1, HEADER-OUT.5, HEADER-OUT.6, J4.26, SCREW-OUT.2, SCREW-OUT2.2, SMA-OUT1.CLK (1), U$10.2, X1.1
AOUT2: BNC-OUT2.1, HEADER-OUT.7, HEADER-OUT.8, J4.25, SCREW-OUT.3, SCREW-OUT2.3, SMA-OUT2.CLK (1), U$11.2
AOUT3: BNC-OUT3.1, HEADER-OUT.9, HEADER-OUT.10, J4.12, SCREW-OUT.4, SCREW-OUT2.4, SMA-OUT3.CLK (1), U$12.2
AOUT4: BNC-OUT4.1, HEADER-OUT.11, HEADER-OUT.12, J4.24, SCREW-OUT.5, SCREW-OUT2.5, SMA-OUT4.CLK (1), U$13.2
AOUT5: BNC-OUT5.1, HEADER-OUT.13, HEADER-OUT.14, J4.11, SCREW-OUT.6, SCREW-OUT2.6, SMA-OUT5.CLK (1), U$14.2
AOUT6: BNC-OUT6.1, HEADER-OUT.15, HEADER-OUT.16, J4.23, SCREW-OUT.7, SCREW-OUT2.7, SMA-OUT6.CLK (1), U$15.2
AOUT7: BNC-OUT7.1, HEADER-OUT.17, HEADER-OUT.18, J4.10, SCREW-OUT.8, SCREW-OUT2.8, SMA-OUT7.CLK (1), U$16.2
GND: J1.2, J1.3 (2), J1.4 (2), J1.5 (2), J2.2, J2.3 (2), J2.4 (2), J2.5 (2), J3.2, J3.3 (2), J3.4 (2), J3.5 (2), J5.2, J5.3 (2), J5.4 (2), J5.5 (2), SMA-IN16.GND$1 (2), SMA-IN16.GND$2 (2), SMA-IN16.GND$3 (2), SMA-IN16.GND$4 (2), SMA-IN17.GND$1 (2), SMA-IN17.GND$2 (2), SMA-IN17.GND$3 (2), SMA-IN17.GND$4 (2), SMA-IN18.GND$1 (2), SMA-IN18.GND$2 (2), SMA-IN18.GND$3 (2), SMA-IN18.GND$4 (2), SMA-IN19.GND$1 (2), SMA-IN19.GND$2 (2), SMA-IN19.GND$3 (2), SMA-IN19.GND$4 (2), TP1.1
unnamed: J1.1, SMA-IN16.CLK (1)
unnamed: J2.1, SMA-IN18.CLK (1)
unnamed: J3.1, SMA-IN19.CLK (1)
unnamed: J5.1, SMA-IN17.CLK (1)

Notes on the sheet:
ANALOG IO
OUT
Use JLC2313 Stackup: https://jlcpcb.com/client/index.html#/impedance. 0.2 mm prepeg
ANALOG

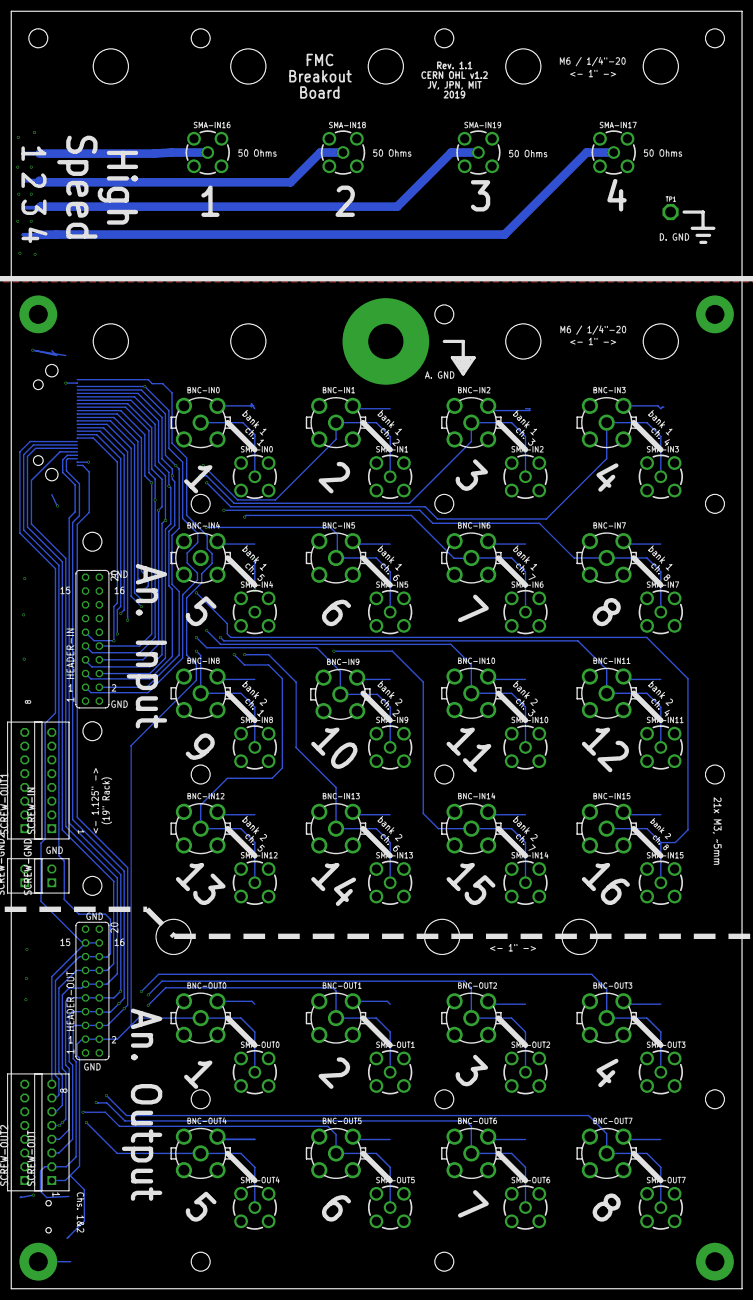
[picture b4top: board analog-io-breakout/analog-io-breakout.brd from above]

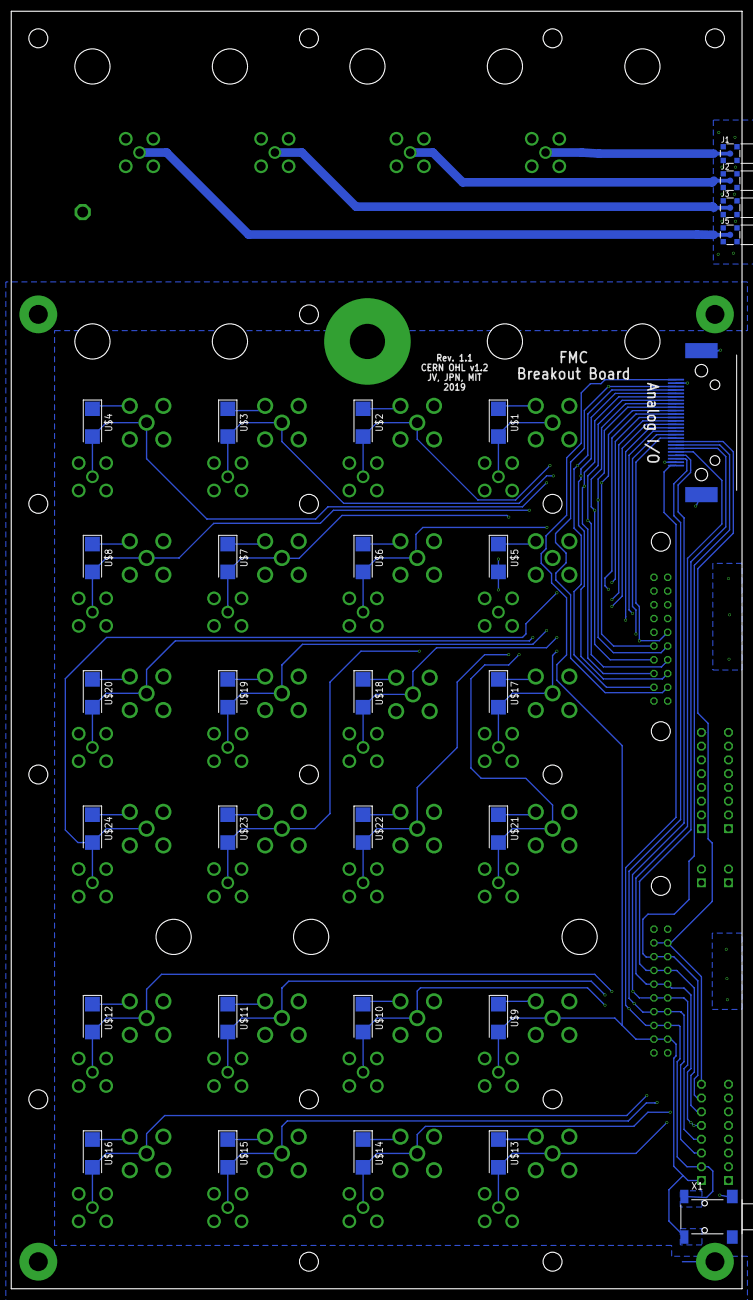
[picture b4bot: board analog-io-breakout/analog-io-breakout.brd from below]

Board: 4 copper layers, 135.0 x 236.0 mm, 91 parts (30 on the bottom side), 30 nets.

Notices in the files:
analog-io-breakout/analog-io-breakout.brd:
CERN OHL v1.2
analog-io-breakout/analog-io-breakout.sch:
LICENSE: CERN OHL v1.2
breakout/revisions/rev-1.5/breakout.brd:
CC BY-NC-SA 4.0
parts and their libraries:
microbuilder: This work is placed in the public domain, and may be freely used for commercial and non-commercial work with the following conditions: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
